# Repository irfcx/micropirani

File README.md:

# Micropirani vacuum gauge
> [!CAUTION]
>Please bear in mind that this is **NOT** a finished thing, and I even guarantee that it will **NOT** work if you reproduce it
## What is this

This is an indirect vacuum gauge based on the thermal conductivity measuring.
Supposed to be small, cheap and easy to reproduce by using small incandescent bulbs as the pressure sensor

## How it (doesn't) works

There are a lot of ways of measuring thermal conductivity, as constant current, constant voltage (or more complex) constant resistance, or even constant power stabilisation with measure of changing values.
In this case the thermal conductivity measure is based on measuring the power required to maintain constant resistance of lamp filament.
The first two (in theory) have drawbacks such as low sensitivity in high vacuum, or increased filament burning when air is rushing into the system quickly, and the last one is too complex, so i stopped on the constant resistance method.

The common CR circuit is a Wheatstone bridge with feedback on the OP. When current flows through the resistors with the same value of resistance, they are equally heated. If for some reason the resistance of one of the resistors changes, the bridge leaves the balance and the operational amplifier compensates this by changing the voltage on the bridge, which in this case is being measured.

As the thermal conductivity of vacuum is way lower than thermal conductivity of air, resistor (open bulb filament) is cooled less and maintaining a constant resistance requires less voltage.
To compensate the ambient temperature change, a sealed bulb is connected in series to the opened. It should be placed as close as possible to the sealed bulb. The STM32 ADC measures the voltage from the bridge that passes through the buffer (it's necessary due to the limitations of the STM's ADC) and converts it into pressure.

STM32F103CBT6 with 128 kB of flash is used as an MCU. It's also worth noting that no significant optimizations were made to reduce the code size, but the firmware still fits in the any 64 kB chip. However, due to the absence of the EEPROM, its emulation is realised using the last 127th page of the flash memory. This is an important point, because in reality even 64 kB chip has 128 kB of memory, but its operability is not declared or guaranteed by ST, so, when using smaller chips its necessary to correct the addressing.

A typical calibration curve looks like an S-curve turned on the side. However, it was not possible to find coefficients and/or digitize it with some other function, so i used the usual table and linear interpolation between points

## Now about the mechanical part

Bulbs are glued to the custom lathe-made KF16 flange from the AISI 316 steel (despite the fact it's still a bottleneck for easy reproducing, you can replace it with cheap KF cap with the hole or whatever you want) using JB weld epoxy, which with that small expose area may be considered suitable for high vacuum

## Now about what I did wrong (and why THIS device is worse than a usual voltmeter with CC circuit)

 - As it was found experimentally, when common (12V?) light bulbs are used, the bridge voltage is changes only in range from 1.4 to 2.8 volts, which is the less than half of the ADC range, so accuracy is very low (although pirani sensors are not accurate in general), and most importantly, the lower measurement range is limited to approximately 10^-3 torr (when the theoretical limit is 10^-5 torr). As the solution, bipolar power supply for the OP can be made (in the next revision probably)
 - The dumbest thing was the use of two (!) linear voltage stabilizers and putting them in the same pcb with the bridge resistors - their heat (up to 70 C) was enough to heat the resistors so the readings drift over time and the calibration is lost when the supply voltage changes
 - The sealed (thermal compensation) bulb MUST be placed as close as possible to the open one, but for some reason they were separated by the whole centimeter of metal.
 - The lack of EM shielding causes the MCU malfunctioning near the vacuum pump when the frequency converter is used to drive the motor
 - The thickness of the metal base of the flange was insufficient so the ends of the PCB stands stick out

https://github.com/irfcx/micropirani/assets/52609749/1622802e-4848-4f7c-a10b-698a371d4f89

## File location

- Kicad pcb and schematic are located in PCB folder
- The main code is located in /source code/Core/Src/source, the main file is micropirani.h
- The compiled firmware binaries are located in /source code/Release
- In case if someone needs it, the fonts are located in /fonts

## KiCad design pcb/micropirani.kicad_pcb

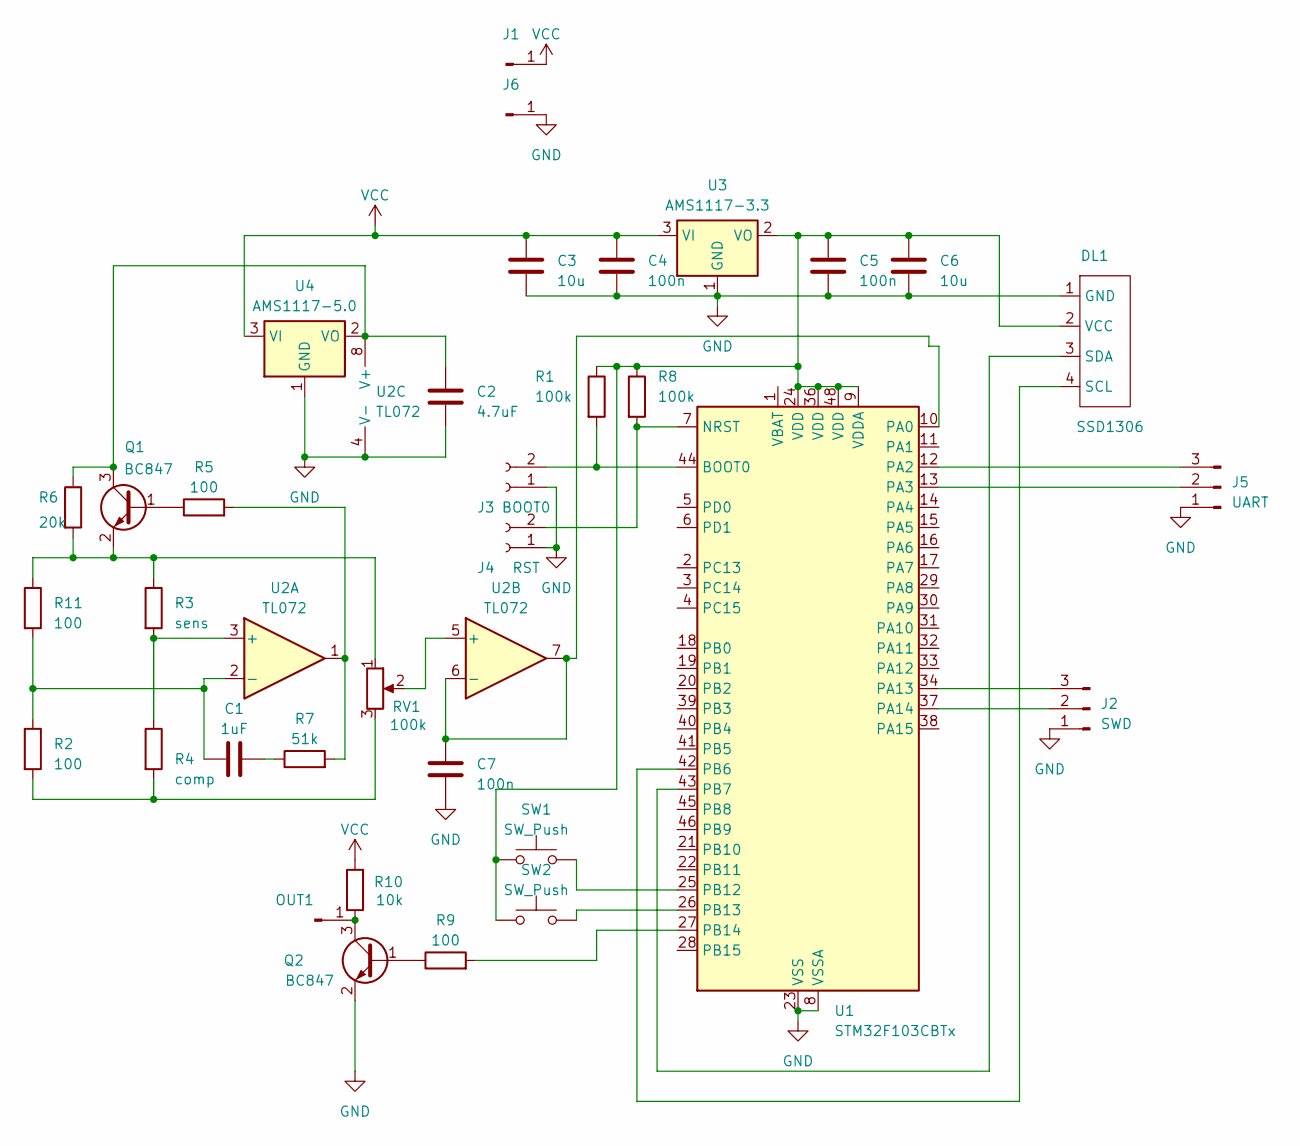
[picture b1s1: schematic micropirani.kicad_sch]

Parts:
C1: 1uF; C_1206_3216Metric
C2: 4.7uF; C_1206_3216Metric
C3, C6: 10u; C_1206_3216Metric
C4, C5, C7: 100n; C_1206_3216Metric
DL1: SSD1306
J1, J6: Conn_01x01_Pin; TestPoint_THTPad_D2.0mm_Drill1.0mm
J2: SWD; SolderJumper-3_P1.3mm_Open_RoundedPad1.0x1.5mm_NumberLabels
J3: BOOT0; SolderJumper-2_P1.3mm_Open_Pad1.0x1.5mm
J4: RST; SolderJumper-2_P1.3mm_Open_Pad1.0x1.5mm
J5: UART; SolderJumper-3_P1.3mm_Open_RoundedPad1.0x1.5mm_NumberLabels
OUT1: Conn_01x01_Pin; TestPoint_THTPad_D2.0mm_Drill1.0mm
Q1, Q2: BC847; SOT-23
R1, R8: 100k; R_1206_3216Metric
R2, R5, R9, R11: 100; R_1206_3216Metric
R3: sens; R_Axial_DIN0204_L3.6mm_D1.6mm_P2.54mm_Vertical
R4: comp; R_Axial_DIN0204_L3.6mm_D1.6mm_P2.54mm_Vertical
R6: 20k; R_1206_3216Metric
R7: 51k; R_1206_3216Metric
R10: 10k; R_1206_3216Metric
RV1: 100k; Potentiometer_Bourns_3214G_Horizontal
SW1, SW2: SW_Push; SW_PUSH_6mm_H13mm
U1: STM32F103CBTx; LQFP-48_7x7mm_P0.5mm
U2: TL072; SO-8_3.9x4.9mm_P1.27mm
U3: AMS1117-3.3; SOT-223-3_TabPin2
U4: AMS1117-5.0; SOT-223-3_TabPin2

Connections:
GND: C2.1, C3.1, C4.1, C5.1, C6.1, C7.1, DL1.1 (GND), J2.1, J3.1, J4.1, J5.1, J6.1, Q2.2 (E), U1.8 (VSSA), U1.23 (VSS), U1.35 (VSS), U1.47 (VSS), U2.4 (V-), U3.1 (GND), U4.1 (GND)
unnamed: C1.2, R7.1
unnamed: DL1.4 (SCL), U1.42 (PB6)
unnamed: DL1.3 (SDA), U1.43 (PB7)
unnamed: C5.2, C6.2, DL1.2 (VCC), R1.1, R8.1, SW1.1, SW2.1, U1.9 (VDDA), U1.24 (VDD), U1.36 (VDD), U1.48 (VDD), U3.2 (VO)
unnamed: J2.2, U1.37 (PA14)
unnamed: J2.3, U1.34 (PA13)
unnamed: J3.2, R1.2, U1.44 (BOOT0)
unnamed: J4.2, R8.2, U1.7 (NRST)
unnamed: J5.2, U1.13 (PA3)
unnamed: J5.3, U1.12 (PA2)
unnamed: OUT1.1, Q2.3 (C), R10.1
unnamed: Q1.1 (B), R5.1
unnamed: C2.2, Q1.3 (C), R6.1, U2.8 (V+), U4.2 (VO)
unnamed: Q1.2 (E), R3.1, R6.2, R11.1, RV1.1
unnamed: Q2.1 (B), R9.1
unnamed: R2.2, R4.2, RV1.3
unnamed: R5.2, R7.2, U2.1
unnamed: C7.2, U1.10 (PA0), U2.6 (-), U2.7
unnamed: SW1.2, U1.25 (PB12)
unnamed: SW2.2, U1.26 (PB13)
unnamed: R9.2, U1.27 (PB14)
unnamed: R3.2, R4.1, U2.3 (+)
unnamed: C1.1, R2.1, R11.2, U2.2 (-)
unnamed: RV1.2, U2.5 (+)
VCC: C3.2, C4.2, J1.1, R10.2, U3.3 (VI), U4.3 (VI)

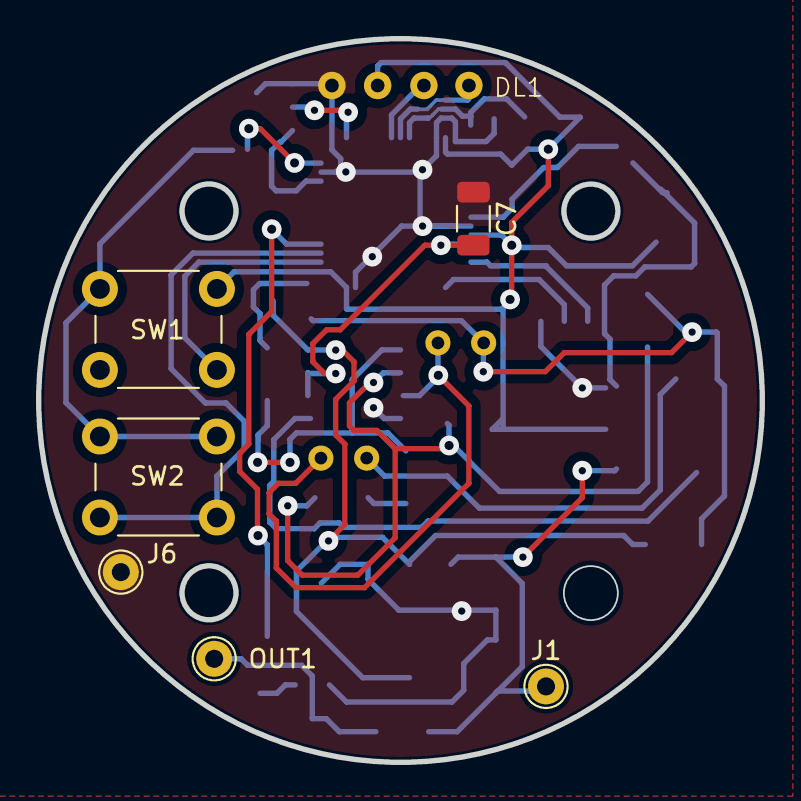
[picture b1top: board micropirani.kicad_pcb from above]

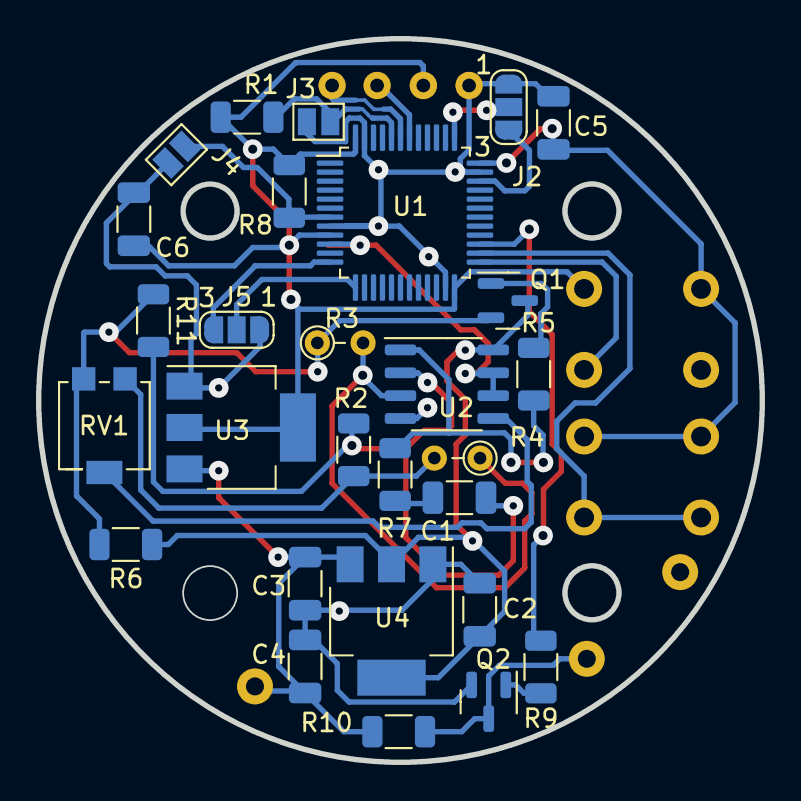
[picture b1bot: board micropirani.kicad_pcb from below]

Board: 2 copper layers, 40.2 x 40.2 mm, 35 parts (28 on the bottom side), 26 nets.

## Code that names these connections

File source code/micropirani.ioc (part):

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Mcu.Name=STM32F103R(8-B)Tx
Mcu.Package=LQFP64
Mcu.UserName=STM32F103RBTx
PA0-WKUP.Signal=ADCx_IN0
PA13.Mode=Serial_Wire
PA13.Signal=SYS_JTMS-SWDIO
PA14.Mode=Serial_Wire
PA14.Signal=SYS_JTCK-SWCLK
PA2.Mode=Asynchronous
PA2.Signal=USART2_TX
PA3.Mode=Asynchronous
PA3.Signal=USART2_RX
PB12.GPIOParameters=GPIO_PuPd,GPIO_ModeDefaultEXTI
PB12.GPIO_ModeDefaultEXTI=GPIO_MODE_IT_FALLING
PB12.GPIO_PuPd=GPIO_PULLDOWN
PB12.Signal=GPXTI12
PB13.GPIOParameters=GPIO_PuPd,GPIO_ModeDefaultEXTI
PB13.GPIO_ModeDefaultEXTI=GPIO_MODE_IT_RISING
PB13.GPIO_PuPd=GPIO_PULLDOWN
PB13.Signal=GPXTI13
PB14.Signal=GPIO_Output
PB6.Mode=I2C
PB6.Signal=I2C1_SCL
PB7.Mode=I2C
PB7.Signal=I2C1_SDA
PC7.Signal=S_TIM3_CH2
RCC.SYSCLKFreq_VALUE=64000000
RCC.SYSCLKSource=RCC_SYSCLKSOURCE_PLLCLK
board=NUCLEO-F103RB
boardIOC=true

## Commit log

2024-06-24 initial
2024-06-24 https://www.heimannsensor.com/vacuum-sensing
